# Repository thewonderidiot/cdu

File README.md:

# CDU Tools and Simulation

This repository contains documentation for, simulations of, and boards for powering and interfacing with the Coupling Data Unit (CDU) from Apollo spacecraft. The CDU performed most analog-to-digital and digital-to-analog conversions for the Apollo Guidance Computer, including resolver-to-digital conversions for the IMU, Command Module optics, and Lunar Module Rendezvous Radar. A breakdown in these conversions was the cause of the 1201 and 1202 program alarms during the Apollo 11 landing. The goal of this project is to replicate that condition on an original CDU, and explain exactly what happened.

## Hardware

### Connector Plate

The main connector of the CDU consists of 300 Malco Mini-Wasp contacts -- not easy to interface with. The connector plate uses Samtec replica contacts to break this connector out into several D-Sub connectors and a bank of test points, enabling much easier interfacing. Each of the five dual resolvers, the Apollo Guidance Computer (AGC), and the Power & Servo Assembly (PSA) get their own dedicated connector. The remaining spacecraft-interfacing signals are placed on one additional connector.

### Resolver Adapter

The resolver used for Apollo is unfortunately essentially unobtainable. It was a dual-speed 1x / 16x resolver driven by 28Vrms at 800Hz. The 1X outputs had amplitudes of approximately 26Vrms, and the 16X outputs had amplitudes of around 5Vrms. Lacking such a resolver, I've cobbled together substitues using modern single-speed resolvers geared together with a 16:1 planetary gearbox, at the cost of some backlash between the speeds. The resolver adapter board connects these two single-speed resolvers to the dual-resolver connectors of the connector plate. It contains compensation capacitors for each resolver, as well as series potentiometers on the reference inputs to fine-tune output amplitudes.

### AGC Simulator

The AGC Simulator contains headers for a [cmod_agc], and adds to it all of the [I/O circuits](https://www.ibiblio.org/apollo/klabs/history/agc_schematics_block2/top_level/a27-a29-1.jpg) required to fully drive the CDU and the PSA.

### Power Supply

The power supply, given 28VDC power in and synchronization signals from the AGC simulator, generates the 28Vrms @ 800Hz and 5Vrms @ 800Hz needed to power the resolvers and the CDU. A second nearly identical power supply chain generates the 15Vrms @ 800Hz representing the ATCA reference. It also incorporates a copy of the PSA's relay logic for startup and mode switching of the CDU. Lastly, it contains some switches from the Lunar Module's control panels relevant to CDU operation, including the fateful Rendezvous Radar mode switch.

In the spirit of the original PSA, the power supply is built with a modular design.

#### AAC, Filter, and Multivibrator Module

This module uses two out-of-phase 800Hz synchronization pulse trains from the AGC to discipline a multivibrator, which chops a reference voltage to produce a square wave. This square wave is passed through a low-pass filter to output a relatively clean ~1Vrms sine wave. The reference voltage is steered by an automatic amplitude control (AAC) circuit connected to the output of the 1% amplifier, boosting or reducing the output until exactly 28Vrms is achieved. The design is almost identical to [the original PSA module](https://archive.org/details/apertureCardBox462NARASW_images/page/n1333/mode/1up), with two key exceptions:
* The factory-chosen AAC tuning resistor has been replaced with a potentiometer
* A zener diode in the reference circuit has been replaced with a LM431 adjustable zener shunt regulator controlled by a potentiometer. This allows the maximum possible output voltage of the module to be tuned, at the cost of some responsiveness in the AAC. The original PSA modules will result in outputs of [more than 52Vrms (!)](https://youtu.be/mxMOano9Zls) at startup -- a level that the system clearly must have been designed to handle, but nevertheless makes me nervous to run into >50-year-old hardware that really wants 28Vrms. I have been tuning my modules to max out at around 32Vrms, which feels much safer.

#### Amplifier 1% 800 CPS Module

This is an original Block I PSA module that is used to boost the ~1Vrms 800Hz output from the AAC, Filter, and Multivibrator Module up to 28Vrms. It can deliver a good bit of power. So far I've been unable to find suitable replacements for its output transformer; so for now I'm simply using the original hardware. This gives the added benefit of driving the CDU and resolvers with AC waveforms of very similar character to the real spacecraft.

#### Fine Reference Module

This module contains a transformer to step down the 28Vrms reference generated by the 1% amplifier down to around 5.6Vrms, as well as an inductor to lightly shift the phase. This lower reference is used to drive the 16X resolvers, which need to have lower outputs than the 1X resolvers.

#### IMU Auxiliary, and Relay Module

This module combines subsets of the PSA IMU Auxiliary Module and the Relay Module onto a single board. It has all of the relay logic required to correctly sequence on the CDU and handle mode switching. It also contains some switches to stimulate discrete inputs to the CDU, including the CAGE switch from one of the LM panels.

#### LM Mode Switching Module

This module contains a simple implementation of the all-important Rendezvous Radar mode switch. The switch changes the rendezvous radar resolver reference voltage outputs from the 28Vrms chain to the 15Vrms chain. The module also includes compensation capacitors to make up for the aging film capacitors in the original 1% amplifiers, and small dummy loads to keep the power supplies happy while not driving anything.

## Simulation

The `sim` folder contains Verilog models of a single channel of the CDU. Digital modules are represented with gate-accurate logical implementations; analog modules are mathematically modeled. Gains for the analog modules have been taken from the appropriate procurement specifications, for maximum accuracy.

The simulator requires [Icarus Verilog](https://github.com/steveicarus/iverilog). It can be built and run with:
```bash
make run
```
from the `sim` directory. Simulation results can be viewed using [GTKWave](https://gtkwave.sourceforge.net/), with
```
gtkwave dump.fst cdu.gtkw
```

## Documentation

The `docs` folder contains stitched drawings and reassembled procurement specifications, pieced together from [invidividual aperture card scans](https://ibiblio.org/apollo/ElectroMechanical.html#Accessing_the_Available_GN_Engineering) from the National Archives at Fort Worth.

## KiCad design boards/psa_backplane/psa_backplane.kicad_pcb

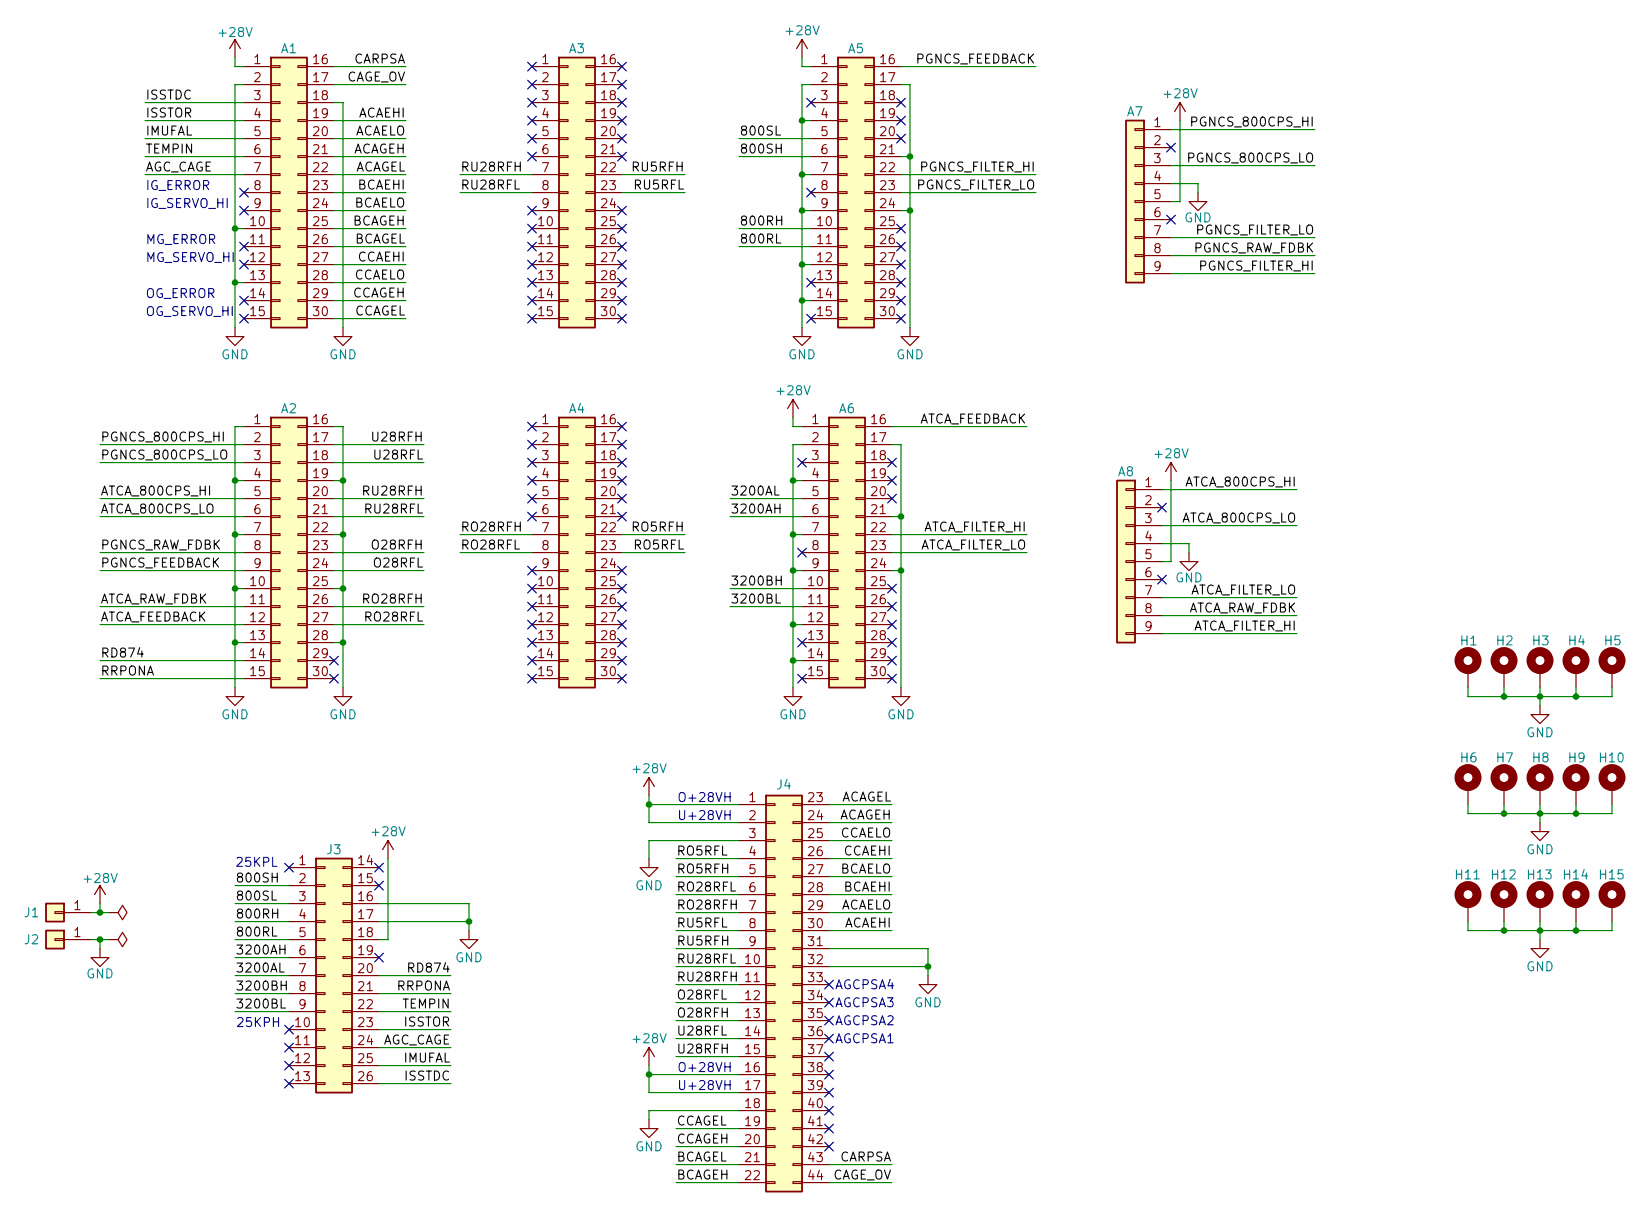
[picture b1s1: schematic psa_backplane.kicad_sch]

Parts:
A1, A2, A3, A4, A5, A6: Conn_02x15_Top_Bottom; PSA_Module
A7, A8: Conn_01x09; PSA_Amp
H1, H2, H3, H4, H5, H6, H7, H8, H9, H10, H11, H12, H13, H14, H15: MountingHole_Pad; MountingHole_No2_Pad
J1: Conn_01x01; Banana_Cliff_FCR7350R_S16N-PC_Horizontal
J2: Conn_01x01; Banana_Cliff_FCR7350B_S16N-PC_Horizontal
J3: Conn_02x13_Top_Bottom; HARTING_HD26_RA
J4: Conn_02x22_Top_Bottom; HARTING_HD44_RA

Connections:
+28V: A1.1, A5.1, A6.1, A7.5, A8.5, J1.1, J3.18, J4.1, J4.2, J4.16, J4.17
/800RH: A5.10, J3.4
/800RL: A5.11, J3.5
/800SH: A5.6, J3.2
/800SL: A5.5, J3.3
/3200AH: A6.6, J3.6
/3200AL: A6.5, J3.7
/3200BH: A6.10, J3.8
/3200BL: A6.11, J3.9
/ACAEHI: A1.19, J4.30
/ACAELO: A1.20, J4.29
/ACAGEH: A1.21, J4.24
/ACAGEL: A1.22, J4.23
/AGC_CAGE: A1.7, J3.24
/ATCA_800CPS_HI: A2.5, A8.1
/ATCA_800CPS_LO: A2.6, A8.3
/ATCA_FEEDBACK: A2.12, A6.16
/ATCA_FILTER_HI: A6.22, A8.9
/ATCA_FILTER_LO: A6.23, A8.7
/ATCA_RAW_FDBK: A2.11, A8.8
/BCAEHI: A1.23, J4.28
/BCAELO: A1.24, J4.27
/BCAGEH: A1.25, J4.22
/BCAGEL: A1.26, J4.21
/CAGE_OV: A1.17, J4.44
/CARPSA: A1.16, J4.43
/CCAEHI: A1.27, J4.26
/CCAELO: A1.28, J4.25
/CCAGEH: A1.29, J4.20
/CCAGEL: A1.30, J4.19
/IMUFAL: A1.5, J3.25
/ISSTDC: A1.3, J3.26
/ISSTOR: A1.4, J3.23
/O28RFH: A2.23, J4.13
/O28RFL: A2.24, J4.12
/PGNCS_800CPS_HI: A2.2, A7.1
/PGNCS_800CPS_LO: A2.3, A7.3
/PGNCS_FEEDBACK: A2.9, A5.16
/PGNCS_FILTER_HI: A5.22, A7.9
/PGNCS_FILTER_LO: A5.23, A7.7
/PGNCS_RAW_FDBK: A2.8, A7.8
/RD874: A2.14, J3.20
/RO5RFH: A4.22, J4.5
/RO5RFL: A4.23, J4.4
/RO28RFH: A2.26, A4.7, J4.7
/RO28RFL: A2.27, A4.8, J4.6
/RRPONA: A2.15, J3.21
/RU5RFH: A3.22, J4.9
/RU5RFL: A3.23, J4.8
/RU28RFH: A2.20, A3.7, J4.11
/RU28RFL: A2.21, A3.8, J4.10
/TEMPIN: A1.6, J3.22
/U28RFH: A2.17, J4.15
/U28RFL: A2.18, J4.14
GND: A1.2, A1.10, A1.13, A1.18, A2.1, A2.4, A2.7, A2.10, A2.13, A2.16, A2.19, A2.22, A2.25, A2.28, A5.2, A5.4, A5.7, A5.9, A5.12, A5.14, A5.17, A5.21, A5.24, A6.2, A6.4, A6.7, A6.9, A6.12, A6.14, A6.17, A6.21, A6.24, A7.4, A8.4, H1.1, H2.1, H3.1, H4.1, H5.1, H6.1, H7.1, H8.1, H9.1, H10.1, H11.1, H12.1, H13.1, H14.1, H15.1, J2.1, J3.16, J3.17, J4.3, J4.18, J4.31, J4.32

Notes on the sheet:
MG_ERROR
OG_ERROR
AGCPSA4
AGCPSA1
MG_SERVO_HI
O+28VH
IG_SERVO_HI
AGCPSA3
IG_ERROR
OG_SERVO_HI
U+28VH
25KPL
AGCPSA2
25KPH

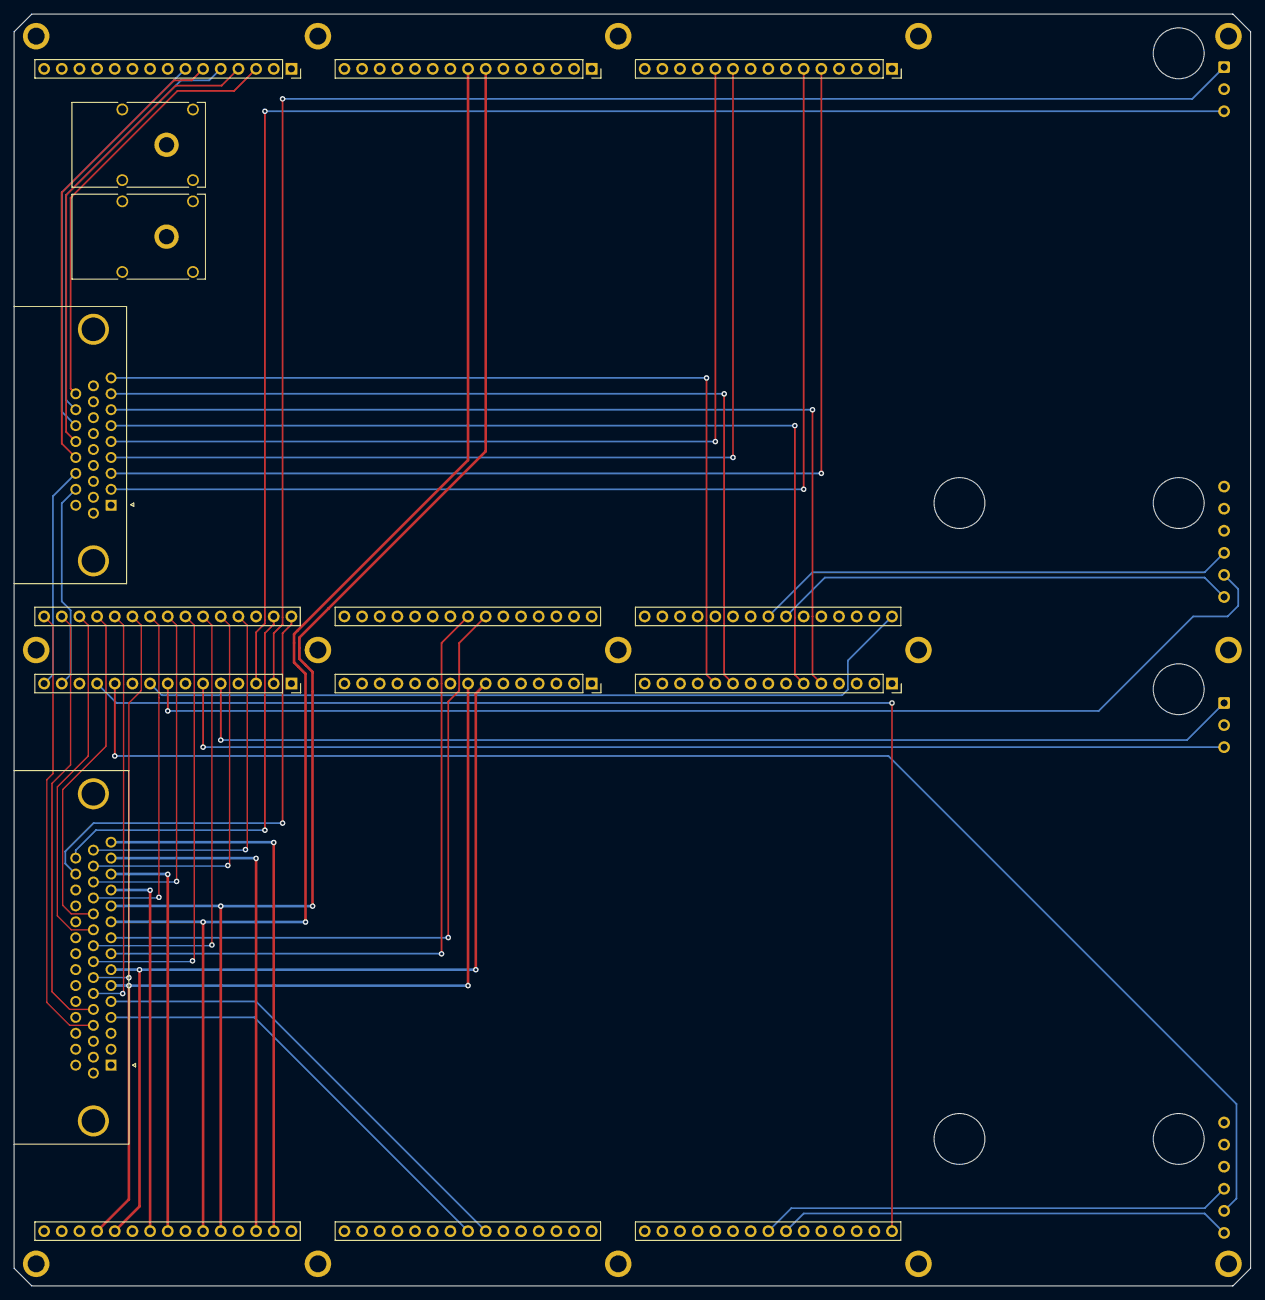
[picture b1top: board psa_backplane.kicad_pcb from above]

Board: 4 copper layers, 177.8 x 182.9 mm, 27 parts (0 on the bottom side), 55 nets.

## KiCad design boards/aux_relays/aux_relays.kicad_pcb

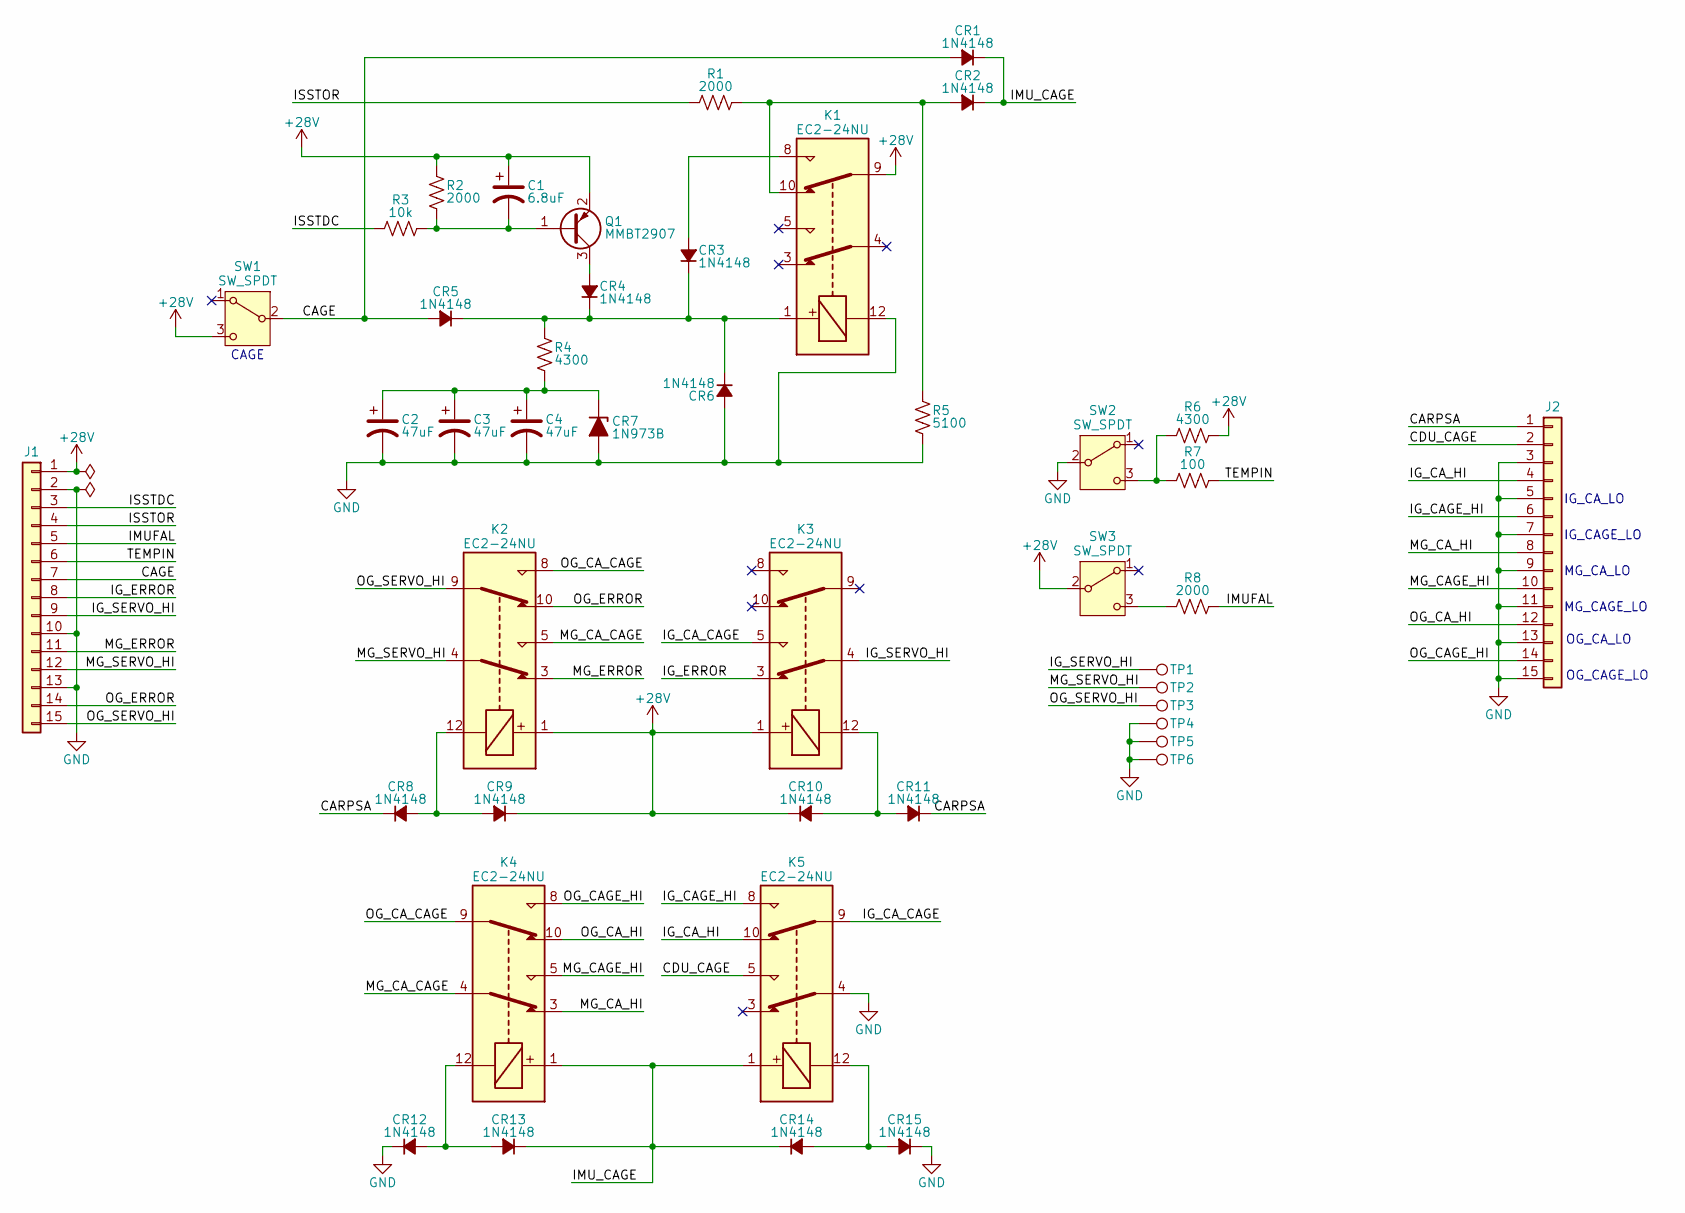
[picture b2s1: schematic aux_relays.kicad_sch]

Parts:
C1: 6.8uF; CP_EIA-7343-31_Kemet-D
C2, C3, C4: 47uF; CP_EIA-7343-43_Kemet-X
CR1, CR2, CR3, CR4, CR5, CR6, CR8, CR9, CR10, CR11, CR12, CR13, CR14, CR15: 1N4148; D_SOD-323
CR7: 1N973B; D_SOD-123
J1, J2: Conn_01x15; PinHeader_1x15_P2.54mm_Vertical
K1, K2, K3, K4, K5: EC2-24NU; Relay_DPDT_Kemet_EC2_NU
Q1: MMBT2907; SOT-23
R1, R2, R8: 2000; R_0603_1608Metric
R3: 10k; R_0603_1608Metric
R4, R6: 4300; R_0603_1608Metric
R5: 5100; R_0603_1608Metric
R7: 100; R_0603_1608Metric
SW1, SW2, SW3: SW_SPDT; E-Switch_100M2_SPDT
TP1, TP2, TP3, TP4, TP5, TP6: TestPoint; TestPoint_Keystone_5000-5004_Miniature

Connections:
+28V: C1.1, CR9.1 (K), CR10.1 (K), J1.1, K1.9, K2.1, K3.1, Q1.2 (E), R2.1, R6.2, SW1.3 (C), SW3.2 (B)
/CAGE: CR1.2 (A), CR5.2 (A), J1.7, SW1.2 (B)
/CARPSA: CR8.1 (K), CR11.1 (K), J2.1
/CDU_CAGE: J2.2, K5.5
/IG_CAGE_HI: J2.6, K5.8
/IG_CA_CAGE: K3.5, K5.9
/IG_CA_HI: J2.4, K5.10
/IG_ERROR: J1.8, K3.3
/IG_SERVO_HI: J1.9, K3.4, TP1.1
/IMUFAL: J1.5, R8.2
/IMU_CAGE: CR1.1 (K), CR2.1 (K), CR13.1 (K), CR14.1 (K), K4.1, K5.1
/ISSTDC: J1.3, R3.1
/ISSTOR: J1.4, R1.1
/MG_CAGE_HI: J2.10, K4.5
/MG_CA_CAGE: K2.5, K4.4
/MG_CA_HI: J2.8, K4.3
/MG_ERROR: J1.11, K2.3
/MG_SERVO_HI: J1.12, K2.4, TP2.1
/OG_CAGE_HI: J2.14, K4.8
/OG_CA_CAGE: K2.8, K4.9
/OG_CA_HI: J2.12, K4.10
/OG_ERROR: J1.14, K2.10
/OG_SERVO_HI: J1.15, K2.9, TP3.1
/TEMPIN: J1.6, R7.2
GND: C2.2, C3.2, C4.2, CR6.2 (A), CR7.2 (A), CR12.1 (K), CR15.1 (K), J1.2, J1.10, J1.13, J2.3, J2.5, J2.7, J2.9, J2.11, J2.13, J2.15, K1.12, K5.4, R5.2, SW2.2 (B), TP4.1, TP5.1, TP6.1
unnamed: CR2.2 (A), K1.10, R1.2, R5.1
unnamed: CR3.2 (A), K1.8
unnamed: CR3.1 (K), CR4.1 (K), CR5.1 (K), CR6.1 (K), K1.1, R4.1
unnamed: CR4.2 (A), Q1.3 (C)
unnamed: C2.1, C3.1, C4.1, CR7.1 (K), R4.2
unnamed: CR8.2 (A), CR9.2 (A), K2.12
unnamed: CR10.2 (A), CR11.2 (A), K3.12
unnamed: CR12.2 (A), CR13.2 (A), K4.12
unnamed: CR14.2 (A), CR15.2 (A), K5.12
unnamed: C1.2, Q1.1 (B), R2.2, R3.2
unnamed: R6.1, R7.1, SW2.3 (C)
unnamed: R8.1, SW3.3 (C)

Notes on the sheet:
IG_CAGE_LO
MG_CAGE_LO
CAGE
OG_CA_LO
IG_CA_LO
MG_CA_LO
OG_CAGE_LO

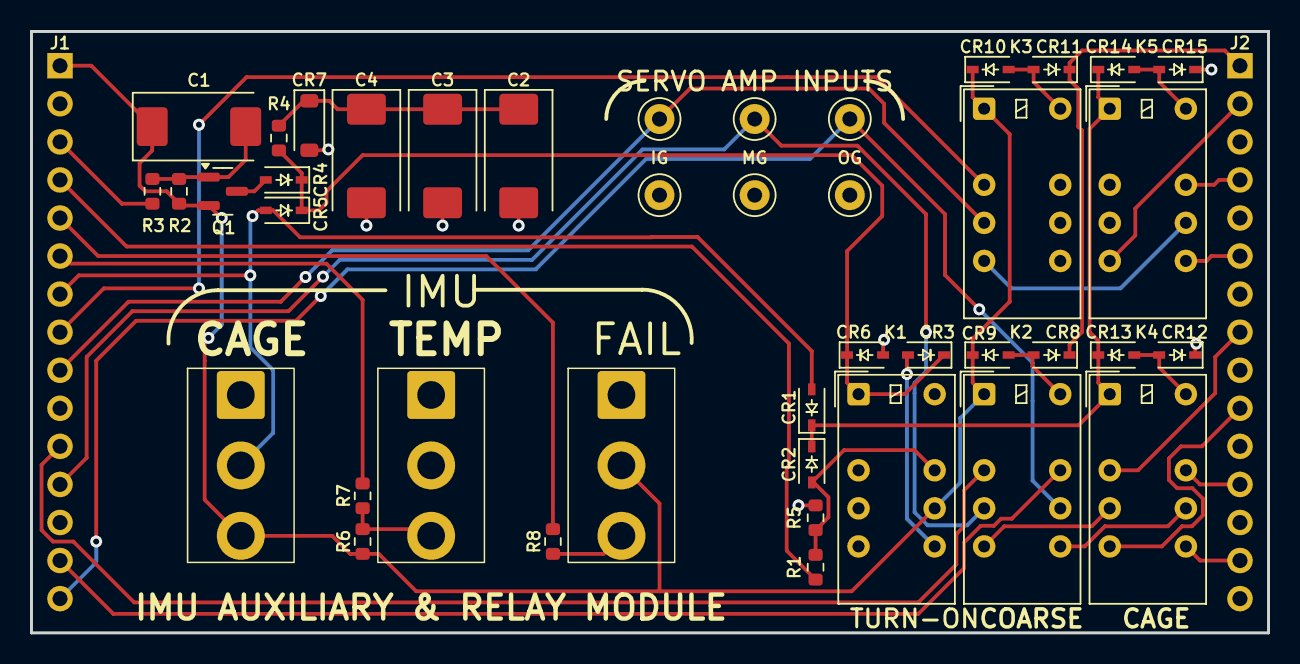
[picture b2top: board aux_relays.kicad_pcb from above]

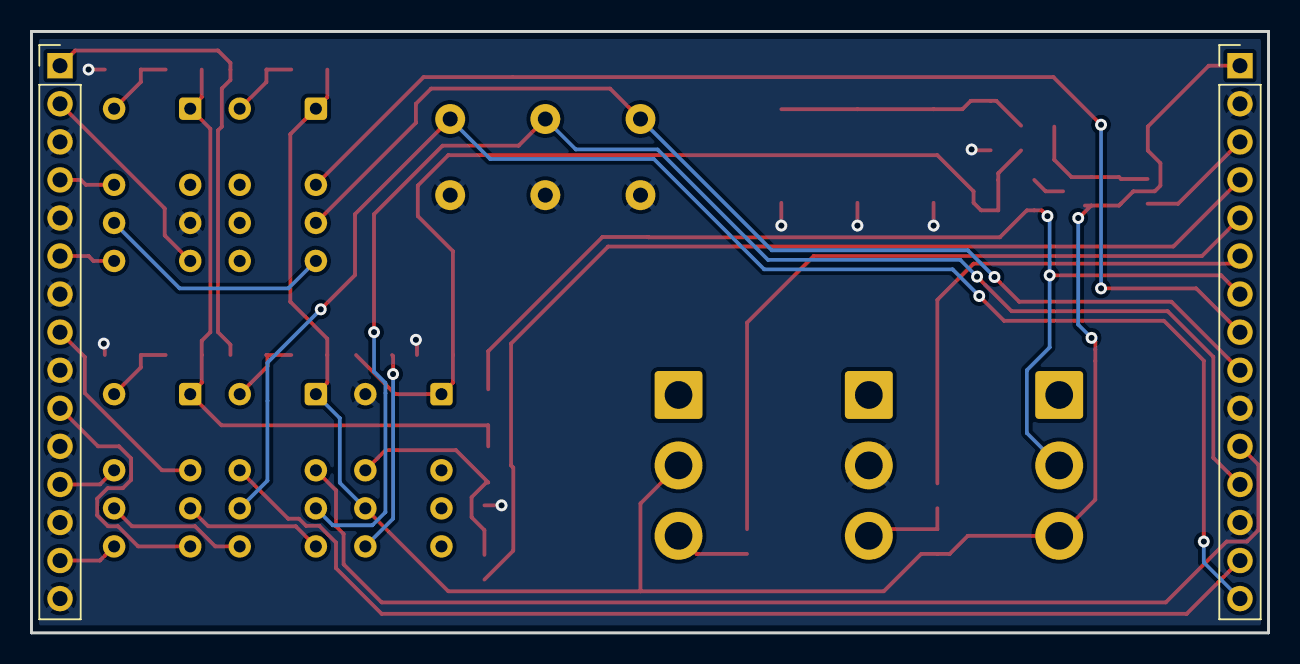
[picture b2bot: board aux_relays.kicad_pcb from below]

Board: 2 copper layers, 82.6 x 40.1 mm, 44 parts (2 on the bottom side), 37 nets.

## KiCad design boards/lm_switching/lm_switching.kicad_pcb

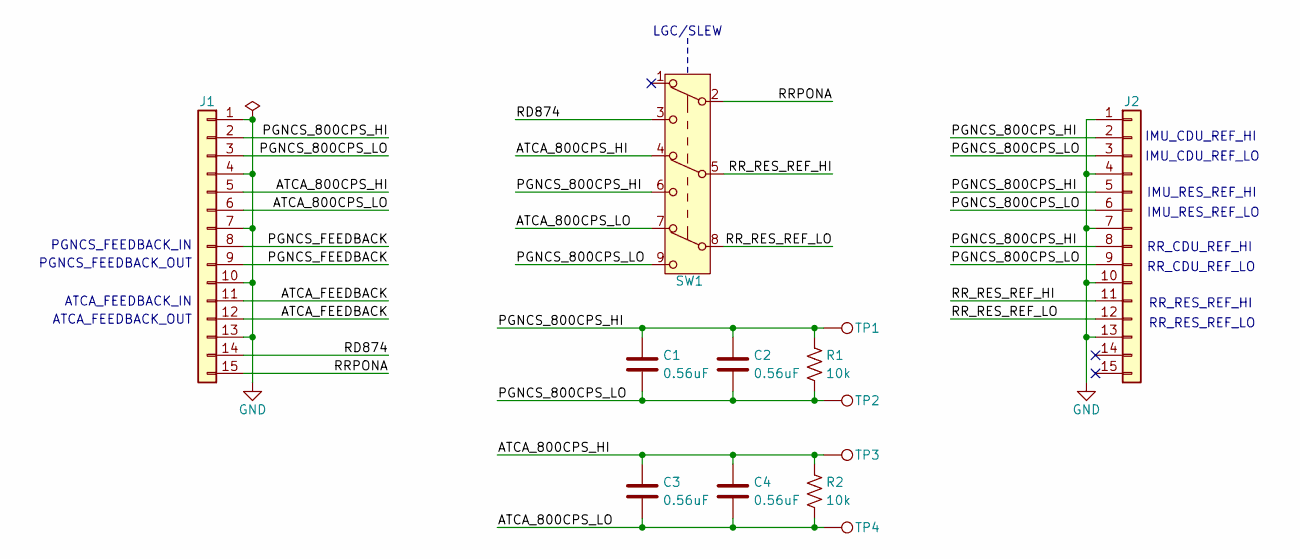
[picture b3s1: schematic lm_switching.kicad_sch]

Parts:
C1, C2, C3, C4: 0.56uF; C_Rect_L13.0mm_W6.0mm_P10.00mm_FKS3_FKP3_MKS4
J1, J2: Conn_01x15; PinHeader_1x15_P2.54mm_Vertical
R1, R2: 10k; R_0805_2012Metric
SW1: SW_3PDT; E-Switch_100M2_3PDT
TP1, TP2, TP3, TP4: TestPoint; TestPoint_Keystone_5000-5004_Miniature

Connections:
/ATCA_800CPS_HI: C3.1, C4.1, J1.5, R2.1, SW1.4 (A), TP3.1
/ATCA_800CPS_LO: C3.2, C4.2, J1.6, R2.2, SW1.7 (A), TP4.1
/ATCA_FEEDBACK: J1.11, J1.12
/PGNCS_800CPS_HI: C1.1, C2.1, J1.2, J2.2, J2.5, J2.8, R1.1, SW1.6 (C), TP1.1
/PGNCS_800CPS_LO: C1.2, C2.2, J1.3, J2.3, J2.6, J2.9, R1.2, SW1.9 (C), TP2.1
/PGNCS_FEEDBACK: J1.8, J1.9
/RD874: J1.14, SW1.3 (C)
/RRPONA: J1.15, SW1.2 (B)
/RR_RES_REF_HI: J2.11, SW1.5 (B)
/RR_RES_REF_LO: J2.12, SW1.8 (B)
GND: J1.1, J1.4, J1.7, J1.10, J1.13, J2.1, J2.4, J2.7, J2.10, J2.13

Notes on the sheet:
RR_RES_REF_HI
LGC/SLEW
IMU_CDU_REF_HI
RR_CDU_REF_LO
RR_CDU_REF_HI
ATCA_FEEDBACK_IN
PGNCS_FEEDBACK_OUT
ATCA_FEEDBACK_OUT
IMU_CDU_REF_LO
PGNCS_FEEDBACK_IN
IMU_RES_REF_HI
RR_RES_REF_LO
IMU_RES_REF_LO

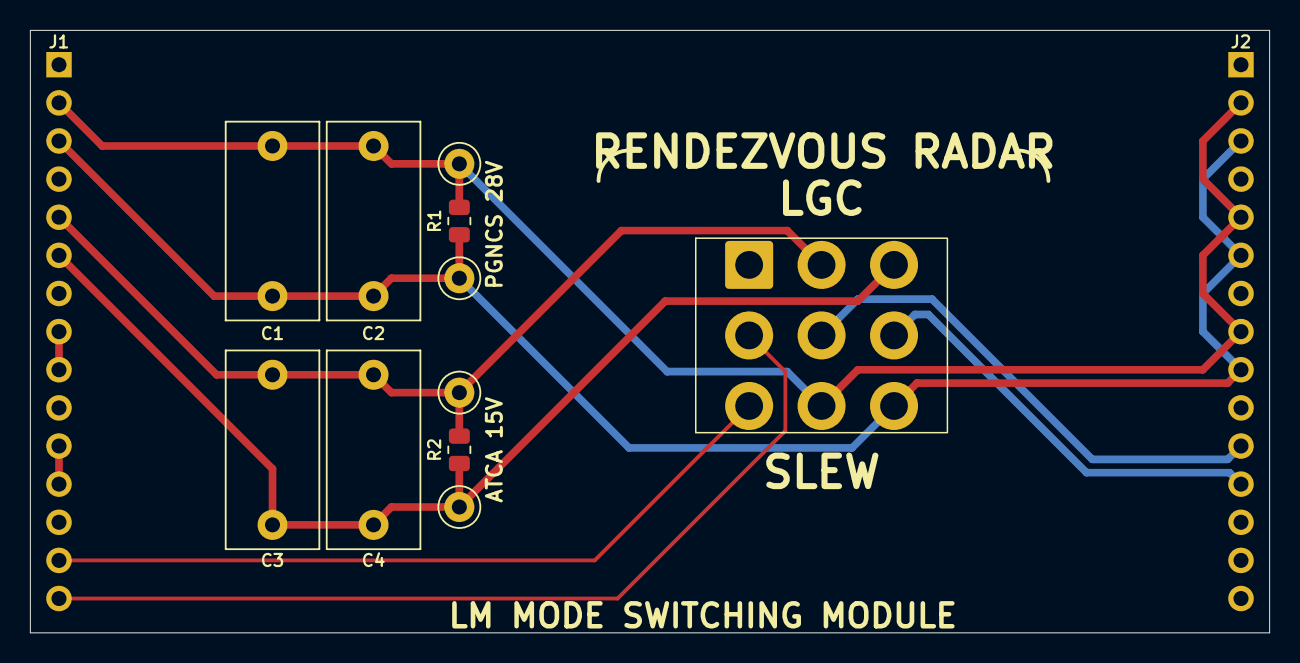
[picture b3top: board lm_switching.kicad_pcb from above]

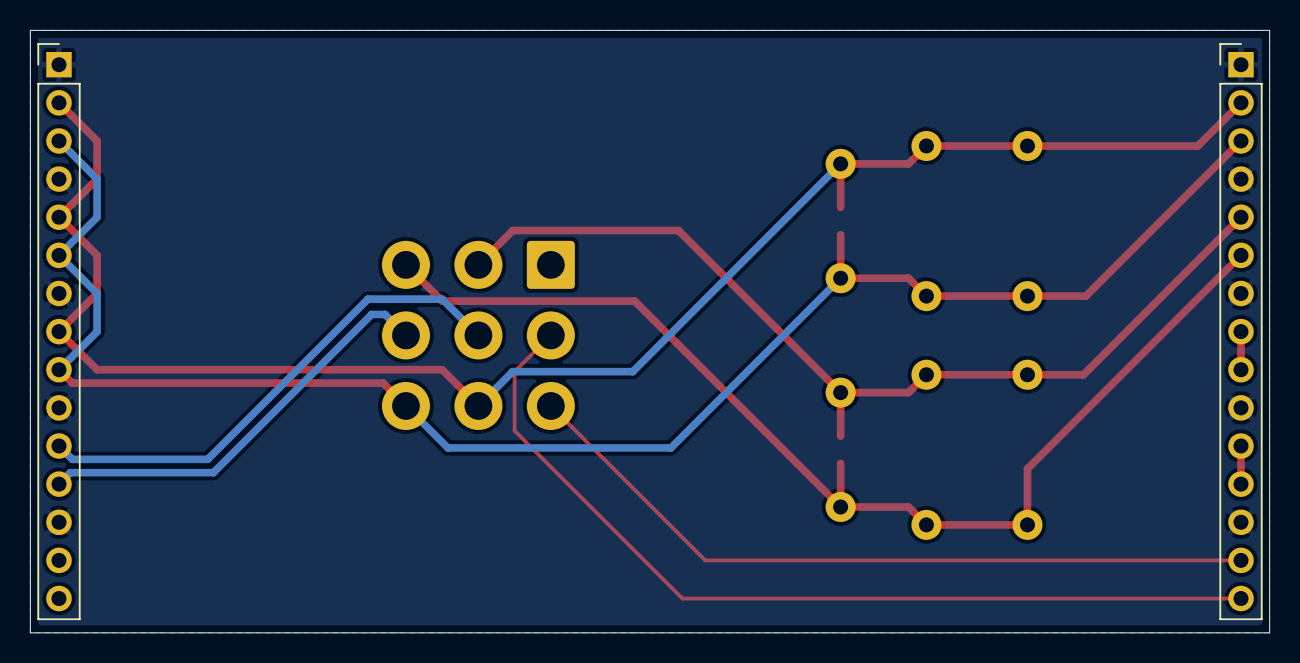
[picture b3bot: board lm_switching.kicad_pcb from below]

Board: 2 copper layers, 82.6 x 40.1 mm, 13 parts (2 on the bottom side), 11 nets.

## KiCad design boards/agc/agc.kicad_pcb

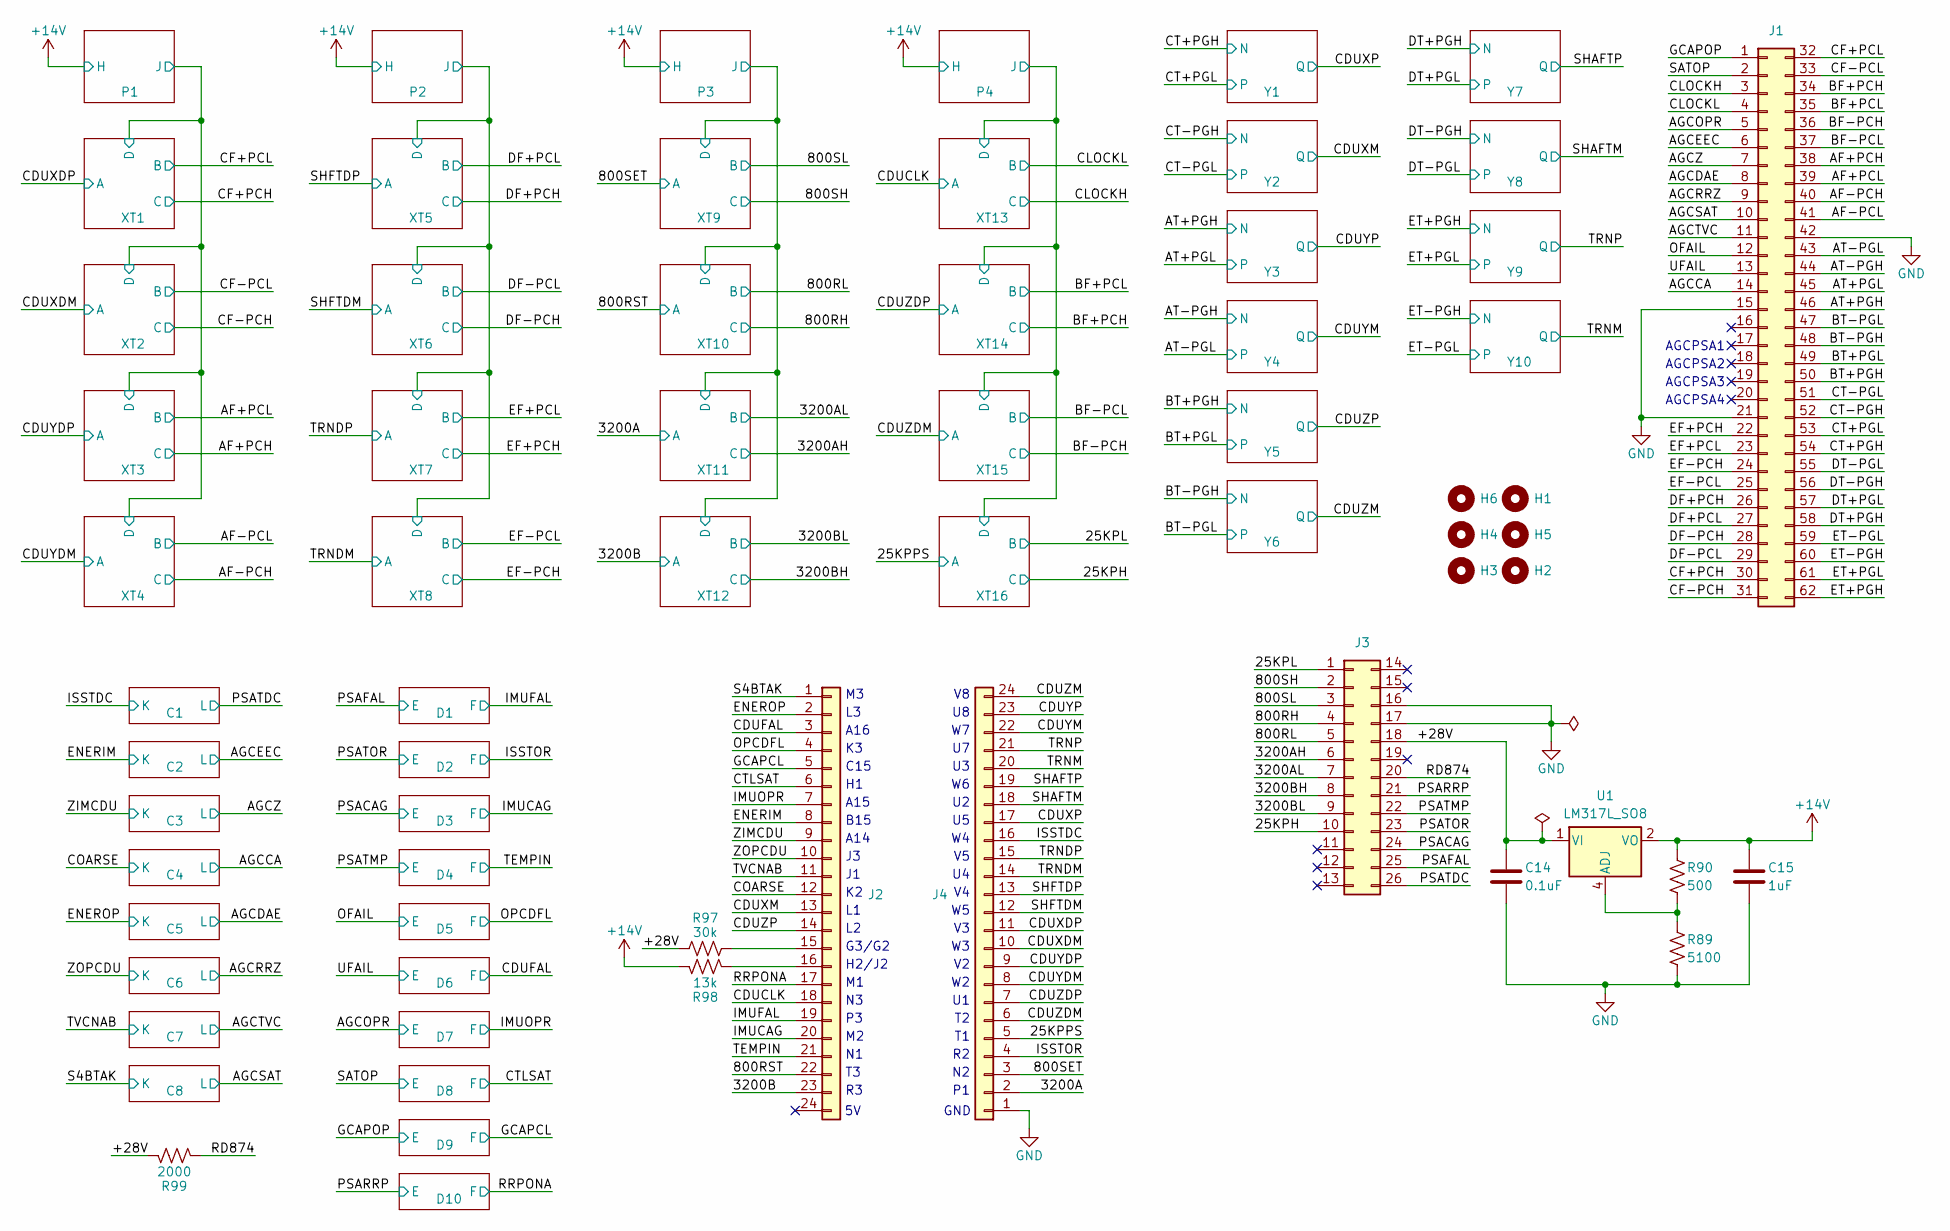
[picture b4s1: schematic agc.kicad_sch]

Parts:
C14: 0.1uF; C_0603_1608Metric
C15: 1uF; C_0603_1608Metric
H1, H2, H3, H4, H5, H6: MountingHole; MountingHole_4-40
J1: Conn_02x31_Top_Bottom; HARTING_HD62_RA
J2, J4: Conn_01x24; PinSocket_1x24_P2.54mm_Vertical; MPN PPPC241LFBN-RC
J3: Conn_02x13_Top_Bottom; HARTING_HD26_RA
R89: 5100; R_0603_1608Metric
R90: 500; R_0603_1608Metric
R97: 30k; R_0603_1608Metric
R98: 13k; R_0603_1608Metric
R99: 2000; R_0603_1608Metric
U1: LM317L_SO8; SOIC-8_3.9x4.9mm_P1.27mm

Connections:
+14V: C15.1, R90.1, R98.1, U1.2 (VO), U1.3 (VO), U1.6 (VO), U1.7 (VO); also elsewhere on the board
/25KPH: J3.10; also elsewhere on the board
/25KPL: J3.1; also elsewhere on the board
/25KPPS: J4.5; also elsewhere on the board
/800RH: J3.4; also elsewhere on the board
/800RL: J3.5; also elsewhere on the board
/800RST: J2.22; also elsewhere on the board
/800SET: J4.3; also elsewhere on the board
/800SH: J3.2; also elsewhere on the board
/800SL: J3.3; also elsewhere on the board
/3200A: J4.2; also elsewhere on the board
/3200AH: J3.6; also elsewhere on the board
/3200AL: J3.7; also elsewhere on the board
/3200B: J2.23; also elsewhere on the board
/3200BH: J3.8; also elsewhere on the board
/3200BL: J3.9; also elsewhere on the board
/+28V: C14.1, J3.18, R97.1, R99.1, U1.1 (VI)
/AF+PCH: J1.38; also elsewhere on the board
/AF+PCL: J1.39; also elsewhere on the board
/AF-PCH: J1.40; also elsewhere on the board
/AF-PCL: J1.41; also elsewhere on the board
/AGCCA: J1.14; also elsewhere on the board
/AGCDAE: J1.8; also elsewhere on the board
/AGCEEC: J1.6; also elsewhere on the board
/AGCOPR: J1.5; also elsewhere on the board
/AGCRRZ: J1.9; also elsewhere on the board
/AGCSAT: J1.10; also elsewhere on the board
/AGCTVC: J1.11; also elsewhere on the board
/AGCZ: J1.7; also elsewhere on the board
/AT+PGH: J1.46; also elsewhere on the board
/AT+PGL: J1.45; also elsewhere on the board
/AT-PGH: J1.44; also elsewhere on the board
/AT-PGL: J1.43; also elsewhere on the board
/BF+PCH: J1.34; also elsewhere on the board
/BF+PCL: J1.35; also elsewhere on the board
/BF-PCH: J1.36; also elsewhere on the board
/BF-PCL: J1.37; also elsewhere on the board
/BT+PGH: J1.50; also elsewhere on the board
/BT+PGL: J1.49; also elsewhere on the board
/BT-PGH: J1.48; also elsewhere on the board
/BT-PGL: J1.47; also elsewhere on the board
/CDUCLK: J2.18; also elsewhere on the board
/CDUFAL: J2.3; also elsewhere on the board
/CDUXDM: J4.10; also elsewhere on the board
/CDUXDP: J4.11; also elsewhere on the board
/CDUXM: J2.13; also elsewhere on the board
/CDUXP: J4.17; also elsewhere on the board
/CDUYDM: J4.8; also elsewhere on the board
/CDUYDP: J4.9; also elsewhere on the board
/CDUYM: J4.22; also elsewhere on the board
/CDUYP: J4.23; also elsewhere on the board
/CDUZDM: J4.6; also elsewhere on the board
/CDUZDP: J4.7; also elsewhere on the board
/CDUZM: J4.24; also elsewhere on the board
/CDUZP: J2.14; also elsewhere on the board
/CF+PCH: J1.30; also elsewhere on the board
/CF+PCL: J1.32; also elsewhere on the board
/CF-PCH: J1.31; also elsewhere on the board
/CF-PCL: J1.33; also elsewhere on the board
/CLOCKH: J1.3; also elsewhere on the board
/CLOCKL: J1.4; also elsewhere on the board
/COARSE: J2.12; also elsewhere on the board
/CT+PGH: J1.54; also elsewhere on the board
/CT+PGL: J1.53; also elsewhere on the board
/CT-PGH: J1.52; also elsewhere on the board
/CT-PGL: J1.51; also elsewhere on the board
/CTLSAT: J2.6; also elsewhere on the board
/DF+PCH: J1.26; also elsewhere on the board
/DF+PCL: J1.27; also elsewhere on the board
/DF-PCH: J1.28; also elsewhere on the board
/DF-PCL: J1.29; also elsewhere on the board
/DT+PGH: J1.58; also elsewhere on the board
/DT+PGL: J1.57; also elsewhere on the board
/DT-PGH: J1.56; also elsewhere on the board
/DT-PGL: J1.55; also elsewhere on the board
/EF+PCH: J1.22; also elsewhere on the board
/EF+PCL: J1.23; also elsewhere on the board
/EF-PCH: J1.24; also elsewhere on the board
/EF-PCL: J1.25; also elsewhere on the board
/ENERIM: J2.8; also elsewhere on the board
/ENEROP: J2.2; also elsewhere on the board
/ET+PGH: J1.62; also elsewhere on the board
/ET+PGL: J1.61; also elsewhere on the board
/ET-PGH: J1.60; also elsewhere on the board
/ET-PGL: J1.59; also elsewhere on the board
/GCAPCL: J2.5; also elsewhere on the board
/GCAPOP: J1.1; also elsewhere on the board
/IMUCAG: J2.20; also elsewhere on the board
/IMUFAL: J2.19; also elsewhere on the board
/IMUOPR: J2.7; also elsewhere on the board
/ISSTDC: J4.16; also elsewhere on the board
/ISSTOR: J4.4; also elsewhere on the board
/OFAIL: J1.12; also elsewhere on the board
/OPCDFL: J2.4; also elsewhere on the board
/PSACAG: J3.24; also elsewhere on the board
/PSAFAL: J3.25; also elsewhere on the board
/PSARRP: J3.21; also elsewhere on the board
/PSATDC: J3.26; also elsewhere on the board
/PSATMP: J3.22; also elsewhere on the board
/PSATOR: J3.23; also elsewhere on the board
/RD874: J3.20, R99.2
/RRPONA: J2.17; also elsewhere on the board
/S4BTAK: J2.1; also elsewhere on the board
/SATOP: J1.2; also elsewhere on the board
/SHAFTM: J4.18; also elsewhere on the board
/SHAFTP: J4.19; also elsewhere on the board
/SHFTDM: J4.12; also elsewhere on the board
/SHFTDP: J4.13; also elsewhere on the board
/TEMPIN: J2.21; also elsewhere on the board
/TRNDM: J4.14; also elsewhere on the board
/TRNDP: J4.15; also elsewhere on the board
/TRNM: J4.20; also elsewhere on the board
/TRNP: J4.21; also elsewhere on the board
/TVCNAB: J2.11; also elsewhere on the board
/UFAIL: J1.13; also elsewhere on the board
/ZIMCDU: J2.9; also elsewhere on the board
/ZOPCDU: J2.10; also elsewhere on the board
GND: C14.2, C15.2, J1.15, J1.21, J1.42, J3.16, J3.17, J4.1, R89.2; also elsewhere on the board
unnamed: J2.15, R97.2
unnamed: J2.16, R98.2
unnamed: R89.1, R90.2, U1.4 (ADJ)

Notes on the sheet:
AGCPSA4
A15
A16
H2/J2
AGCPSA3
C15
AGCPSA1
B15
G3/G2
AGCPSA2
A14
GND

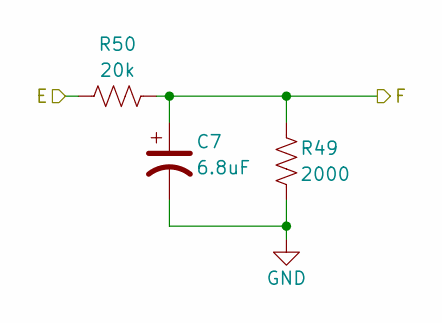
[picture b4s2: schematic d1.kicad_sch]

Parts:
C7: 6.8uF; CP_EIA-7343-31_Kemet-D
R49: 2000; R_0603_1608Metric
R50: 20k; R_0603_1608Metric

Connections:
/IMUFAL: C7.1, R49.2, R50.2; also elsewhere on the board
/PSAFAL: R50.1; also elsewhere on the board
GND: C7.2, R49.1; also elsewhere on the board

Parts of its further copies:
C1, C2, C3, C4, C5, C9, C11, C12, C16: 6.8uF; CP_EIA-7343-31_Kemet-D
R1, R3, R5, R7, R14, R59, R65, R79, R95: 2000; R_0603_1608Metric
R2, R4, R6, R8, R15, R60, R66, R80, R96: 20k; R_0603_1608Metric

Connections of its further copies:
/AGCOPR: R8.1; also elsewhere on the board
/CDUFAL: C5.1, R14.2, R15.2; also elsewhere on the board
/CTLSAT: C2.1, R3.2, R4.2; also elsewhere on the board
/GCAPCL: C1.1, R1.2, R2.2; also elsewhere on the board
/GCAPOP: R2.1; also elsewhere on the board
/IMUCAG: C9.1, R59.2, R60.2; also elsewhere on the board
/IMUOPR: C4.1, R7.2, R8.2; also elsewhere on the board
/ISSTOR: C11.1, R65.2, R66.2; also elsewhere on the board
/OFAIL: R6.1; also elsewhere on the board
/OPCDFL: C3.1, R5.2, R6.2; also elsewhere on the board
/PSACAG: R60.1; also elsewhere on the board
/PSARRP: R96.1; also elsewhere on the board
/PSATMP: R80.1; also elsewhere on the board
/PSATOR: R66.1; also elsewhere on the board
/RRPONA: C16.1, R95.2, R96.2; also elsewhere on the board
/SATOP: R4.1; also elsewhere on the board
/TEMPIN: C12.1, R79.2, R80.2; also elsewhere on the board
/UFAIL: R15.1; also elsewhere on the board
GND: C1.2, C2.2, C3.2, C4.2, C5.2, C9.2, C11.2, C12.2, C16.2, R1.1, R3.1, R5.1, R7.1, R14.1, R59.1, R65.1, R79.1, R95.1; also elsewhere on the board

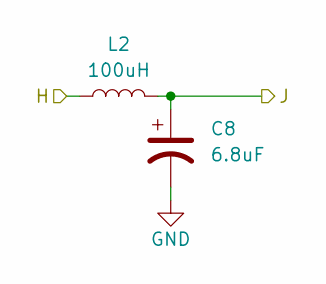
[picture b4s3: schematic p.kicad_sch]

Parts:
C8: 6.8uF; CP_EIA-7343-31_Kemet-D
L2: 100uH; API_Delevan_1812R

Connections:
+14V: L2.1; also elsewhere on the board
/P1/J: C8.1, L2.2; also elsewhere on the board
GND: C8.2; also elsewhere on the board

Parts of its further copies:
C6, C10, C13: 6.8uF; CP_EIA-7343-31_Kemet-D
L1, L3, L4: 100uH; API_Delevan_1812R

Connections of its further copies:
+14V: L1.1, L3.1, L4.1; also elsewhere on the board
/P2/J: C6.1, L1.2; also elsewhere on the board
/P3/J: C13.1, L4.2; also elsewhere on the board
/P4/J: C10.1, L3.2; also elsewhere on the board
GND: C6.2, C10.2, C13.2; also elsewhere on the board
